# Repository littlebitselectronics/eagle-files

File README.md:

# The littleBits Eagle Files Repository

This repository contains the Eagle boards and schematics for all the littleBits modules.

littleBits circuit designs are made available pursuant to the CERN Open Hardware License Version 1.2.  This means that we publish the design files for those modules right here on github. Sharing this stuff is really important to us because littleBits products are an educational tool. Since the circuit designs for our modules are available, students can learn how they work, right down to a circuit level.  This means that people can play with littleBits modules to learn basic circuits and then come back to them later in their education for a deeper understanding of electronics or engineering.  Our founder, Ayah Bdeir, was also one of the founders of the Open Hardware Summit, a major proponent of Open Source Hardware.
To be clear, other intellectual property rights such as design elements like fonts, white soldermask with purple silkscreen, logos, as well as the modular connection system (including the connectors, the connector system and the system of modular circuits) are reserved by littleBits Electronics, Inc., and we have a number of issued patents and pending patent applications related to our proprietary magnetic connectors and our system of electrical circuits.
littleBits is a growing library of pre-assembled electronic circuits that snap together with tiny magnets. Learn more at [littlebits.cc](http://littleBits.cc).

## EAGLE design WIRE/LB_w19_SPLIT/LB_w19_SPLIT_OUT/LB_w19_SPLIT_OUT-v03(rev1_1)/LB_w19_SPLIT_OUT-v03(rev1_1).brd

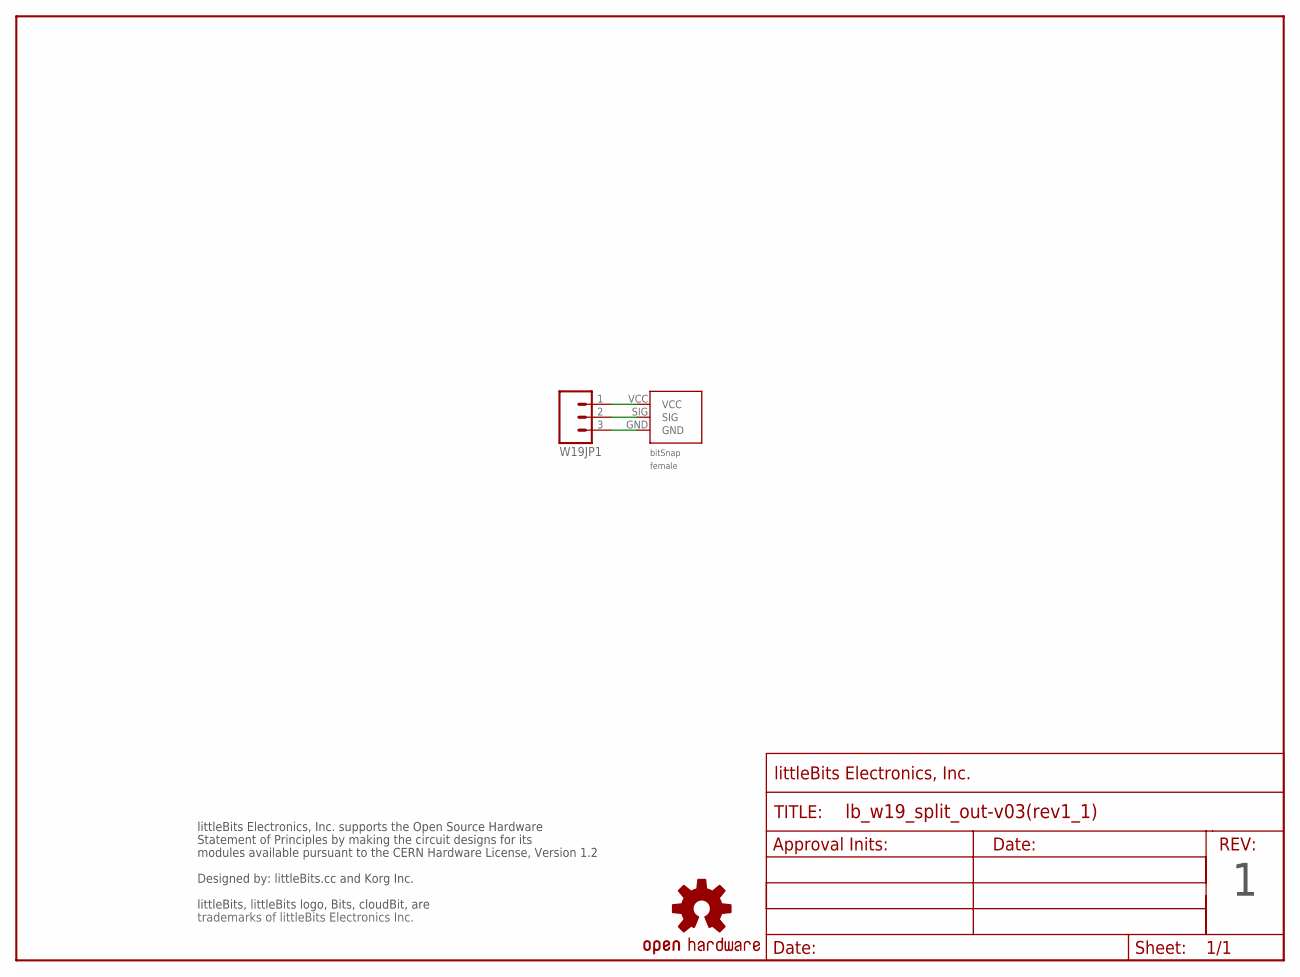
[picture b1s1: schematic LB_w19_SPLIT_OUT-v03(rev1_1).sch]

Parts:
FRAME1: FRAME-LETTER-OHWOHW; FABDWG01-OHW
U$1: OSHWCREDIT-KORG
U$3: OSHW-LOGOL; OSHW-LOGO-L
W19BSF1: BITSNAP_V03_FEMALE
W19JP1: M03SMD; 1X03-1MM-RA

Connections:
GND: W19BSF1.GND, W19JP1.3
SIG: W19BSF1.SIG, W19JP1.2
VCC: W19BSF1.VCC, W19JP1.1

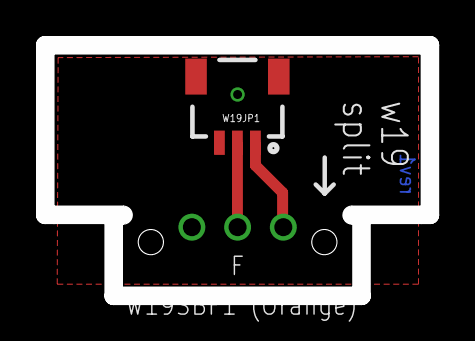
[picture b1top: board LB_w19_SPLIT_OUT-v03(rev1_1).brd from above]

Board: 2 copper layers, 21.4 x 13.9 mm, 6 parts (0 on the bottom side), 3 nets.

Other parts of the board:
U$2: OSHW_FILLX150_NOTEXT

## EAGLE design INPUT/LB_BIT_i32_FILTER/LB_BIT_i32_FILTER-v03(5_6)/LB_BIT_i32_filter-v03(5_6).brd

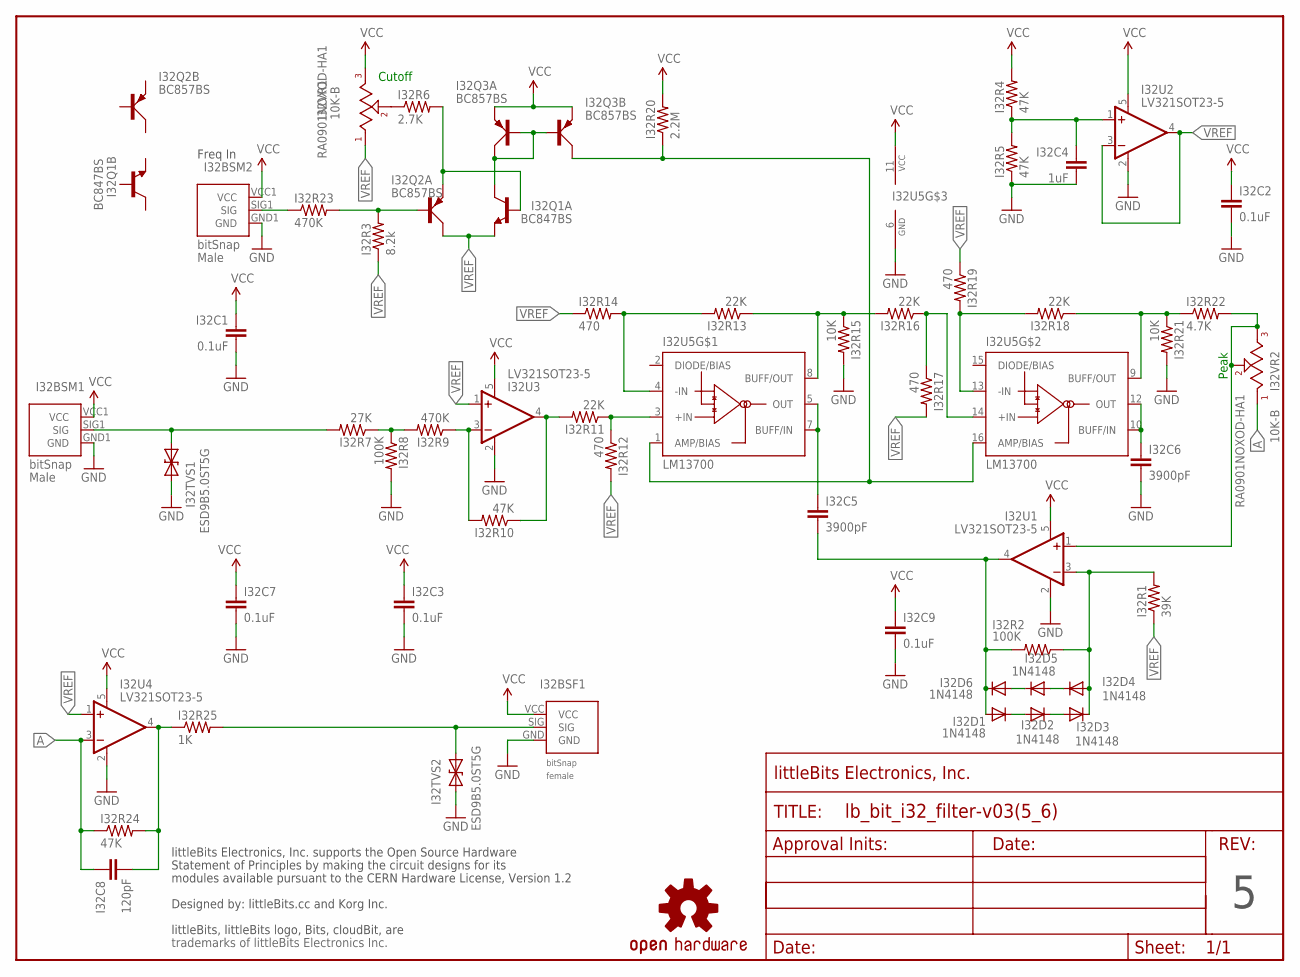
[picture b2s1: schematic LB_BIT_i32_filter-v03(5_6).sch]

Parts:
I32BSF1: BITSNAP_V03_FEMALE
I32BSM1, I32BSM2: BITSNAP_V03_MALE
I32C1, I32C2, I32C3, I32C7, I32C9: 0.1uF; CAP-0603
I32C4: 1uF; CAP-0603
I32C5, I32C6: 3900pF; CAP-0603
I32C8: 120pF; CAP-0603
I32D1, I32D2, I32D3, I32D4, I32D5, I32D6: 1N4148; SOD-323
I32Q1: BC847BS; SOT-363_PHILLIPS
I32Q2, I32Q3: BC857BS; SOT-363_PHILLIPS
I32R1: 39K; RES-0603
I32R2, I32R8: 100K; RES-0603
I32R3: 8.2k; RES-0603
I32R4, I32R5, I32R10, I32R24: 47K; RES-0603
I32R6: 2.7K; RES-0603
I32R7: 27K; RES-0603
I32R9, I32R23: 470K; RES-0603
I32R11, I32R13, I32R16, I32R18: 22K; RES-0603
I32R12, I32R14, I32R17, I32R19: 470; RES-0603
I32R15, I32R21: 10K; RES-0603
I32R20: 2.2M; RES-0603
I32R22: 4.7K; RES-0603
I32R25: 1K; RES-0603
I32TVS1, I32TVS2: ESD9B5.0ST5G; SOD-923
I32U1, I32U2, I32U3, I32U4: LV321SOT23-5; SOT23-5
I32U5: LM13700; DMP16
I32VR1, I32VR2: 10K-B; ALPS_POT
U$1: FRAME-LETTER-OHWOHW; FABDWG01-OHW
U$2: OSHWCREDIT-KORG
U$3: OSHW-LOGOL; OSHW-LOGO-L

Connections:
A: I32C8.1, I32R24.1, I32U4.3 (-IN), I32VR2.1
GND: I32BSF1.GND, I32BSM1.GND1 (GND), I32BSM2.GND1 (GND), I32C1.2, I32C2.2, I32C3.2, I32C4.2, I32C6.2, I32C7.2, I32C9.2, I32R5.1, I32R8.2, I32R15.2, I32R21.2, I32TVS1.1 (A), I32TVS2.1 (A), I32U1.2 (V-), I32U2.2 (V-), I32U3.2 (V-), I32U4.2 (V-), I32U5.6 (GND)
unnamed: I32C4.1, I32R4.1, I32R5.2, I32U2.1 (+IN)
unnamed: I32BSM1.SIG1 (SIG), I32R7.2, I32TVS1.2 (C)
unnamed: I32R6.1, I32VR1.2
unnamed: I32BSF1.SIG, I32R25.2, I32TVS2.2 (C)
unnamed: I32Q1.2 (B), I32Q2.1 (E), I32R6.2
unnamed: I32C5.2, I32D1.2 (A), I32D6.1 (C), I32R2.2, I32U1.4 (OUT)
unnamed: I32R11.1, I32R12.1, I32U5.3 (+IN)
unnamed: I32Q3.3 (C), I32R20.1, I32U5.1 (AMP/BIAS), I32U5.16 (AMP/BIAS)
unnamed: I32R7.1, I32R8.1, I32R9.2
unnamed: I32R9.1, I32R10.2, I32U3.3 (-IN)
unnamed: I32R10.1, I32R11.2, I32U3.4 (OUT)
unnamed: I32R13.2, I32R14.2, I32U5.4 (-IN)
unnamed: I32R18.2, I32R19.2, I32U5.13 (-IN)
unnamed: I32R13.1, I32R15.1, I32R16.2, I32U5.8 (BUFF/OUT)
unnamed: I32C5.1, I32U5.5 (OUT), I32U5.7 (BUFF/IN)
unnamed: I32R22.2, I32U1.1 (+IN), I32VR2.2, I32VR2.3
unnamed: I32R16.1, I32R17.1, I32U5.14 (+IN)
unnamed: I32R18.1, I32R21.1, I32R22.1, I32U5.9 (BUFF/OUT)
unnamed: I32C6.1, I32U5.10 (BUFF/IN), I32U5.12 (OUT)
unnamed: I32C8.2, I32R24.2, I32R25.1, I32U4.4 (OUT)
unnamed: I32D3.1 (C), I32D4.2 (A), I32R1.2, I32R2.1, I32U1.3 (-IN)
unnamed: I32Q2.2 (B), I32R3.2, I32R23.2
unnamed: I32BSM2.SIG1 (SIG), I32R23.1
unnamed: I32D4.1 (C), I32D5.2 (A)
unnamed: I32D5.1 (C), I32D6.2 (A)
unnamed: I32D1.1 (C), I32D2.2 (A)
unnamed: I32D2.1 (C), I32D3.2 (A)
unnamed: I32Q1.6 (C), I32Q3.2 (B), I32Q3.5 (B), I32Q3.6 (C)
VCC: I32BSF1.VCC, I32BSM1.VCC1 (VCC), I32BSM2.VCC1 (VCC), I32C1.1, I32C2.1, I32C3.1, I32C7.1, I32C9.1, I32Q3.1 (E), I32Q3.4 (E), I32R4.2, I32R20.2, I32U1.5 (V+), I32U2.5 (V+), I32U3.5 (V+), I32U4.5 (V+), I32U5.11 (VCC), I32VR1.3
VREF: I32Q1.1 (E), I32Q2.6 (C), I32R1.1, I32R3.1, I32R12.2, I32R14.1, I32R17.2, I32R19.1, I32U2.3 (-IN), I32U2.4 (OUT), I32U3.1 (+IN), I32U4.1 (+IN), I32VR1.1

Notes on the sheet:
Peak
Cutoff
Freq In
RA0901NOXOD-HA1

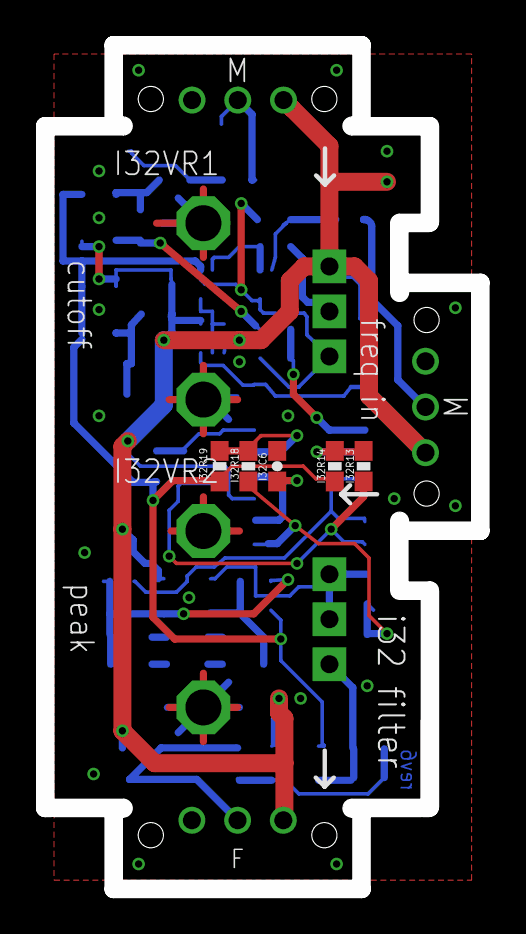
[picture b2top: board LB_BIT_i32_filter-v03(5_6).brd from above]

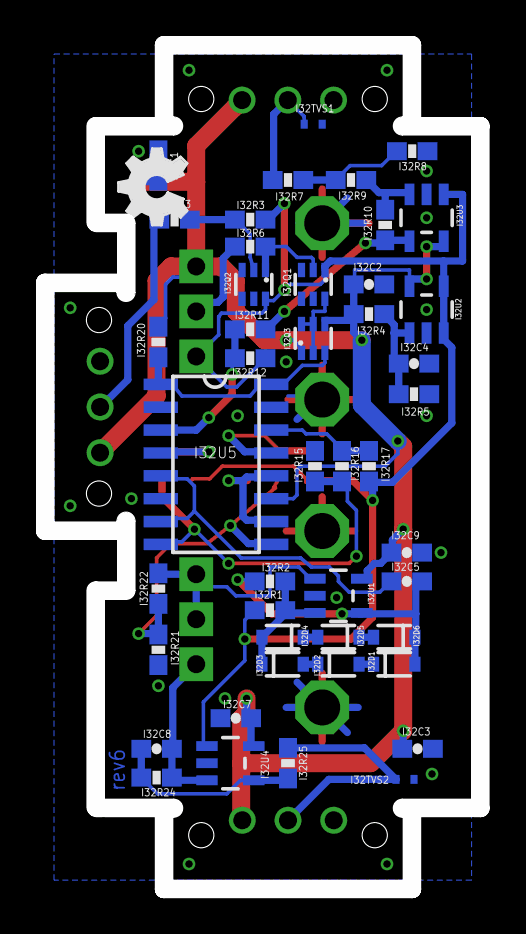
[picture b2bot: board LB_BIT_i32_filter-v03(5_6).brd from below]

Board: 2 copper layers, 24.2 x 46.9 mm, 59 parts (45 on the bottom side), 32 nets.

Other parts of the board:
U$8: OSHW_FILLX150_NOTEXT

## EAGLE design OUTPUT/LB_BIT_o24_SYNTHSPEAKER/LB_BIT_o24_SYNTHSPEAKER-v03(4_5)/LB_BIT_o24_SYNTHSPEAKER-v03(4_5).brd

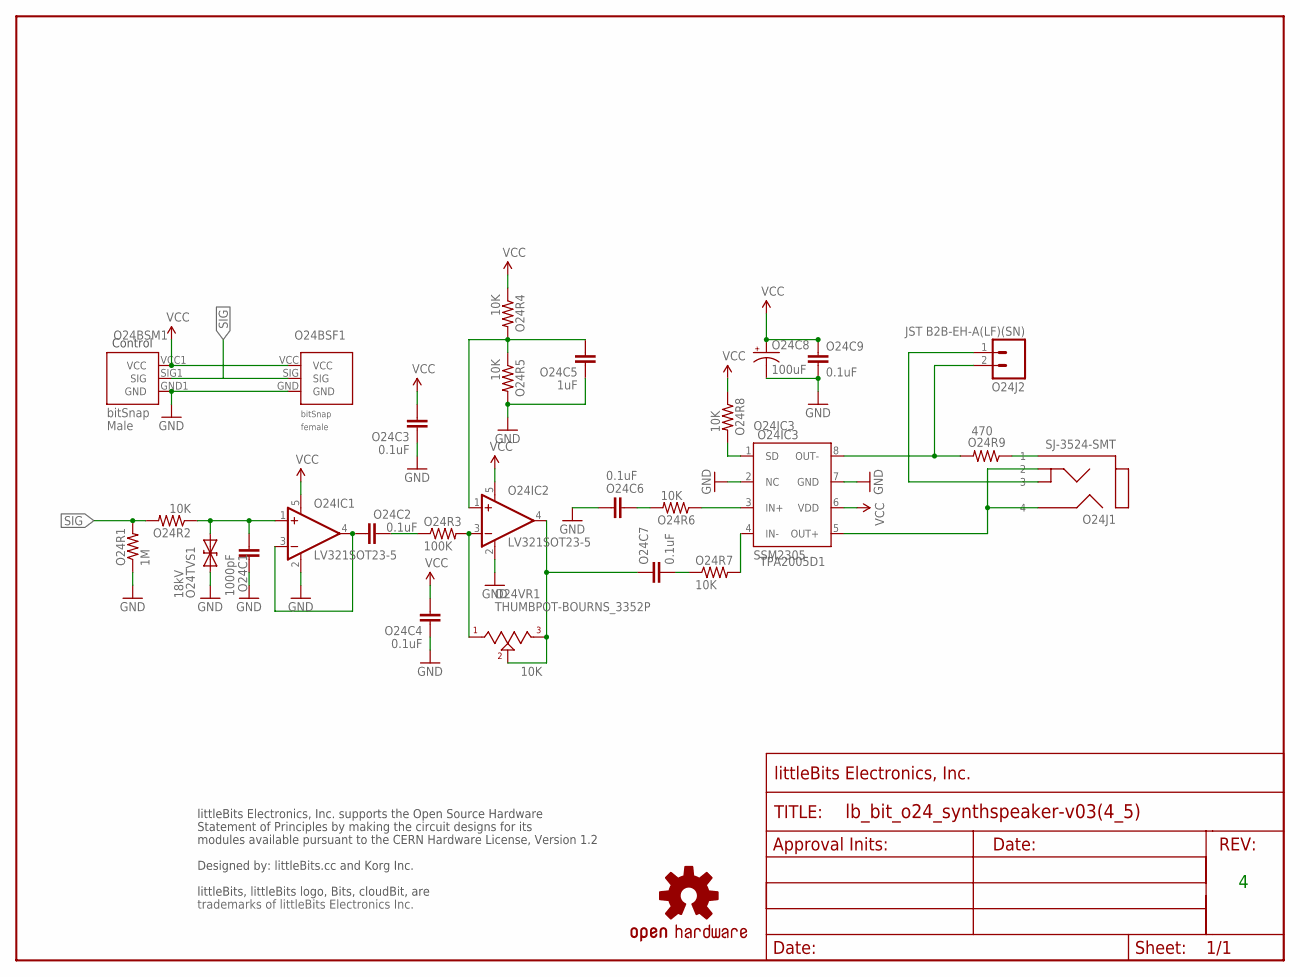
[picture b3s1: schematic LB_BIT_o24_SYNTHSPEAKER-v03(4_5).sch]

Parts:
$1_28_$: OSHW-LOGOL; OSHW-LOGO-L
FRAME1: FRAME-LETTER-OHWOHW; FABDWG01-OHW
O24BSF1: BITSNAP_V03_FEMALE
O24BSM1: BITSNAP_V03_MALE
O24C1: 1000pF; CAP-0603
O24C2, O24C3, O24C4, O24C6, O24C7, O24C9: 0.1uF; CAP-0603
O24C5: 1uF; CAP-0603
O24C8: 100uF; EIA3216
O24IC1, O24IC2: LV321SOT23-5; SOT23-5
O24IC3: SSM2305; MSOP08
O24J1: SJ-3524-SMT; PHONO_JACK_SW
O24J2: JST B2B-EH-A(LF)(SN); H02-JST-B2B-EH-A
O24R1: 1M; RES-0603
O24R2, O24R4, O24R5, O24R6, O24R7, O24R8: 10K; RES-0603
O24R3: 100K; RES-0603
O24R9: 470; RES-0603
O24TVS1: 18kV; SOD-923
O24VR1: THUMBPOT-BOURNS_3352P; THUMBPOT-BOURNS_3352
U$1: OSHWCREDIT-KORG

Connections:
BIT_SIG: O24C2.2, O24IC1.3 (-IN), O24IC1.4 (OUT)
GND: O24BSF1.GND, O24BSM1.GND1 (GND), O24C1.1, O24C3.1, O24C4.1, O24C5.1, O24C6.2, O24C8.-, O24C9.2, O24IC1.2 (V-), O24IC2.2 (V-), O24IC3.2 (NC), O24IC3.7 (GND), O24R1.1, O24R5.2, O24TVS1.1 (A)
unnamed: O24J1.3, O24J2.1
unnamed: O24IC3.1 (SD), O24R8.2
unnamed: O24IC3.5 (OUT+), O24J1.2, O24J1.4
unnamed: O24C6.1, O24R6.2
unnamed: O24J1.1, O24R9.1
unnamed: O24IC3.3 (IN+), O24R6.1
unnamed: O24IC2.3 (-IN), O24R3.2, O24VR1.3 (1)
unnamed: O24C7.1, O24IC2.4 (OUT), O24VR1.1 (3), O24VR1.2
unnamed: O24C5.2, O24IC2.1 (+IN), O24R4.2, O24R5.1
unnamed: O24C7.2, O24R7.1
unnamed: O24C2.1, O24R3.1
unnamed: O24IC3.4 (IN-), O24R7.2
unnamed: O24C1.2, O24IC1.1 (+IN), O24R2.1, O24TVS1.2 (C)
SIG: O24BSF1.SIG, O24BSM1.SIG1 (SIG), O24R1.2, O24R2.2
SPKR_SW: O24IC3.8 (OUT-), O24J2.2, O24R9.2
VCC: O24BSF1.VCC, O24BSM1.VCC1 (VCC), O24C3.2, O24C4.2, O24C8.+, O24C9.1, O24IC1.5 (V+), O24IC2.5 (V+), O24IC3.6 (VDD), O24R4.1, O24R8.1

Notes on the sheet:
TPA2005D1
Control
10K
O24IC3

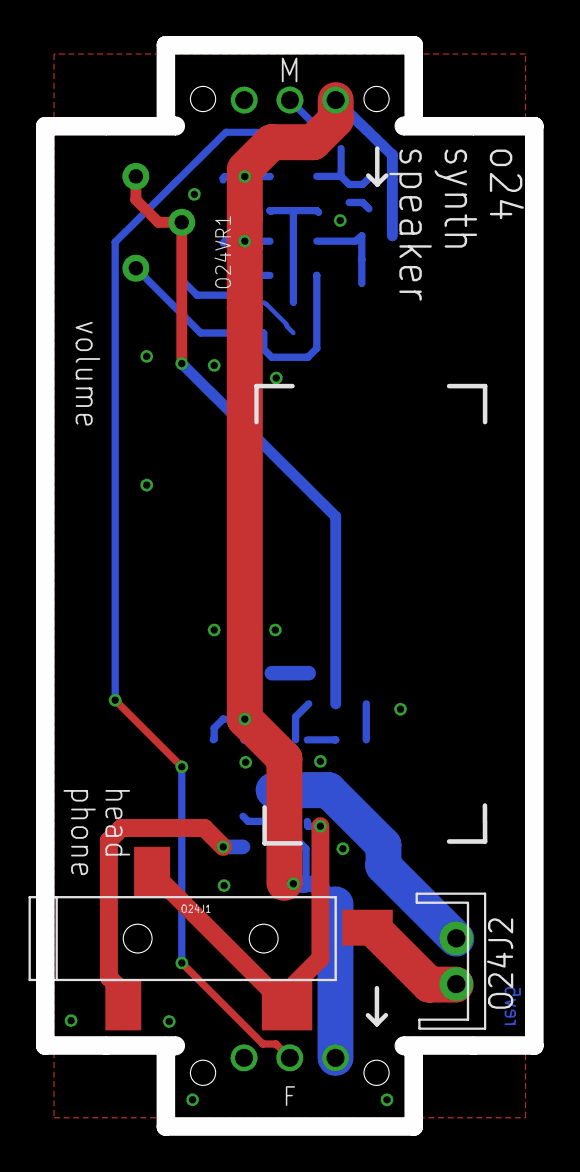
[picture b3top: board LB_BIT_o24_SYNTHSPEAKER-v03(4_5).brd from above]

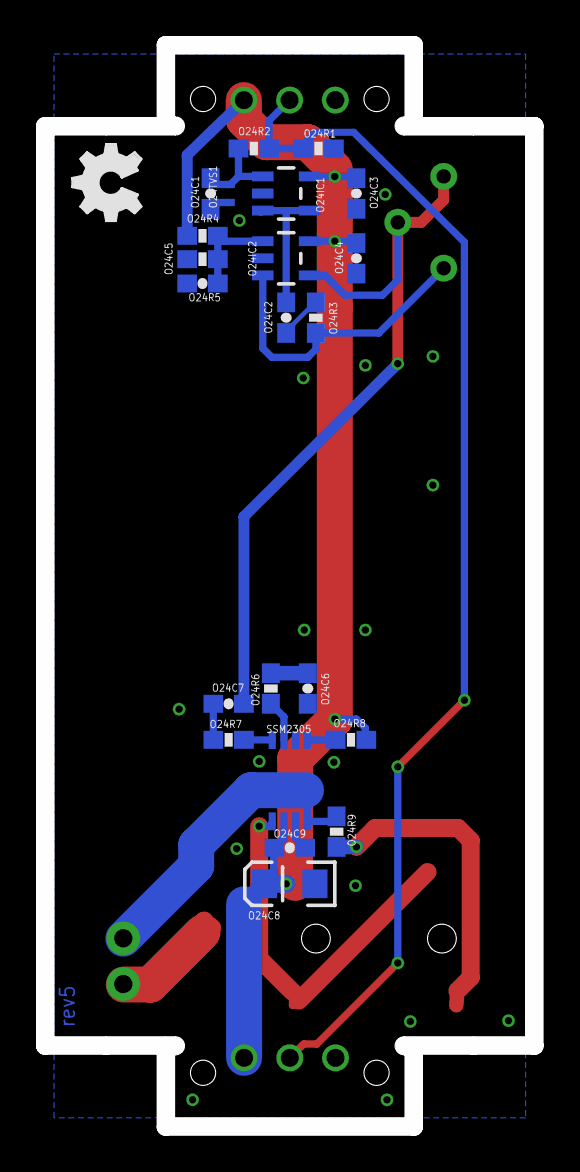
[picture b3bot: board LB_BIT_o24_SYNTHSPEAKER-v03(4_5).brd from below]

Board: 2 copper layers, 27.2 x 60.1 mm, 31 parts (22 on the bottom side), 18 nets.

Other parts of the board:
U$8: OSHW_FILLX150_NOTEXT

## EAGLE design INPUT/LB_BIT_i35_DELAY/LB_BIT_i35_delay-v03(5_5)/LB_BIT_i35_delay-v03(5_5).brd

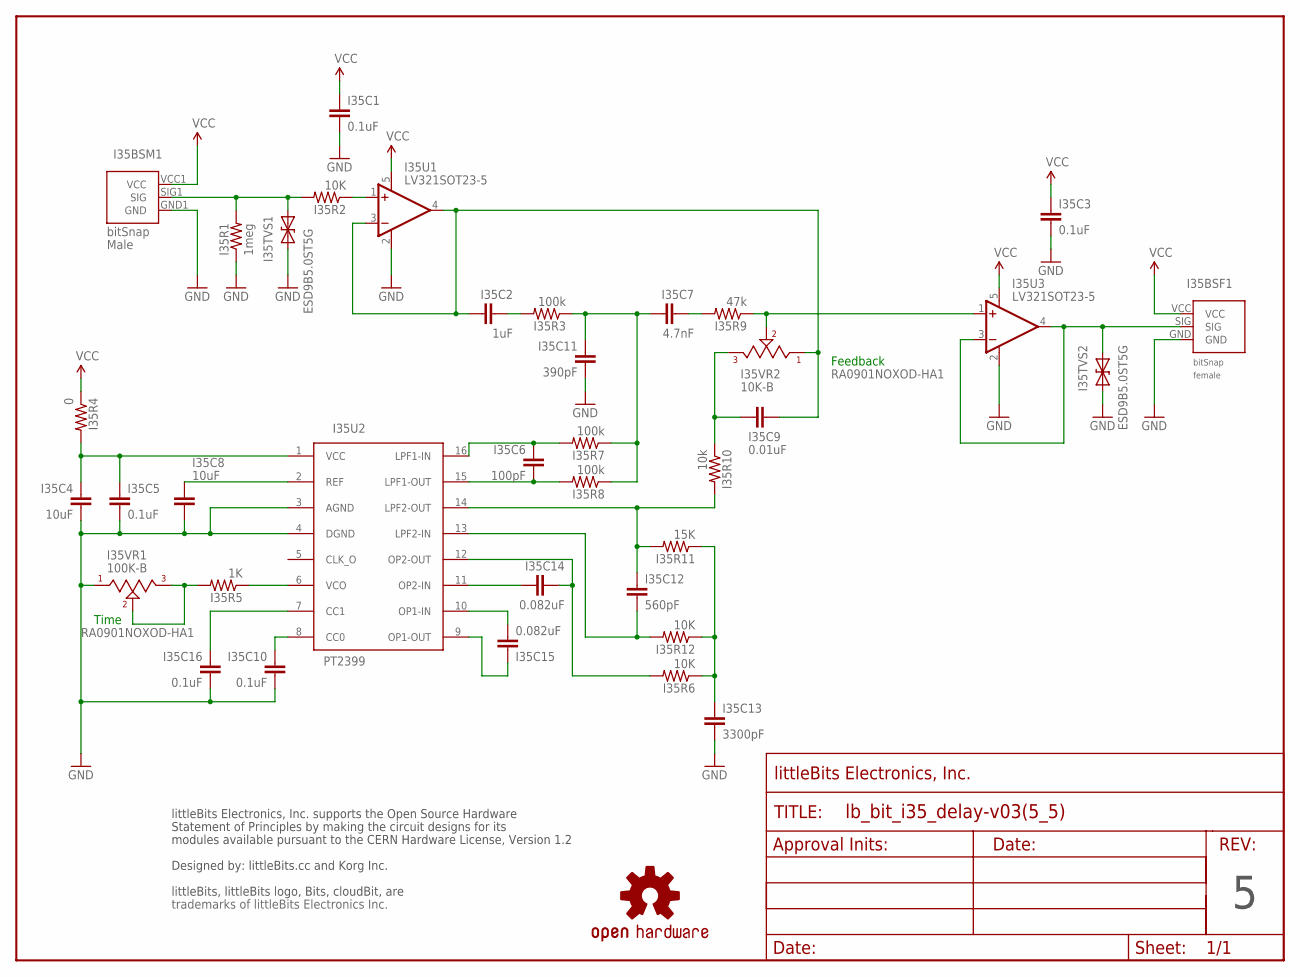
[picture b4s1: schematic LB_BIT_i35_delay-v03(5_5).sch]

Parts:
I35BSF1: BITSNAP_V03_FEMALE
I35BSM1: BITSNAP_V03_MALE
I35C1, I35C3, I35C5, I35C10, I35C16: 0.1uF; CAP-0603
I35C2: 1uF; CAP-0603
I35C4, I35C8: 10uF; CAP-0603
I35C6: 100pF; CAP-0603
I35C7: 4.7nF; CAP-0603
I35C9: 0.01uF; CAP-0603
I35C11: 390pF; CAP-0603
I35C12: 560pF; CAP-0603
I35C13: 3300pF; CAP-0603
I35C14, I35C15: 0.082uF; CAP-0603
I35R1: 1meg; RES-0603
I35R2, I35R6, I35R12: 10K; RES-0603
I35R3, I35R7, I35R8: 100k; RES-0603
I35R4: 0; RES-0603
I35R5: 1K; RES-0603
I35R9: 47k; RES-0603
I35R10: 10k; RES-0603
I35R11: 15K; RES-0603
I35TVS1, I35TVS2: ESD9B5.0ST5G; SOD-923
I35U1, I35U3: LV321SOT23-5; SOT23-5
I35U2: PT2399; SO16
I35VR1: 100K-B; ALPS_POT
I35VR2: 10K-B; ALPS_POT
U$1: FRAME-LETTER-OHWOHW; FABDWG01-OHW
U$2: OSHWCREDIT-KORG
U$3: OSHW-LOGOL; OSHW-LOGO-L

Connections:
GND: I35BSF1.GND, I35BSM1.GND1 (GND), I35C1.2, I35C3.2, I35C4.2, I35C5.2, I35C8.2, I35C10.2, I35C11.2, I35C13.2, I35C16.2, I35R1.1, I35TVS1.1 (A), I35TVS2.1 (A), I35U1.2 (V-), I35U2.3 (AGND), I35U2.4 (DGND), I35U3.2 (V-), I35VR1.1
unnamed: I35C2.2, I35R3.2
unnamed: I35R2.1, I35U1.1 (+IN)
unnamed: I35C7.1, I35C11.1, I35R3.1, I35R7.1, I35R8.1
unnamed: I35C6.2, I35R8.2, I35U2.15 (LPF1-OUT)
unnamed: I35C6.1, I35R7.2, I35U2.16 (LPF1-IN)
unnamed: I35R9.1, I35U3.1 (+IN), I35VR2.2
unnamed: I35C7.2, I35R9.2
unnamed: I35C9.1, I35R10.1, I35VR2.3
unnamed: I35C2.1, I35C9.2, I35U1.3 (-IN), I35U1.4 (OUT), I35VR2.1
unnamed: I35C12.1, I35R10.2, I35R11.2, I35U2.14 (LPF2-OUT)
unnamed: I35C12.2, I35R12.2, I35U2.13 (LPF2-IN)
unnamed: I35C13.1, I35R6.1, I35R11.1, I35R12.1
unnamed: I35C14.2, I35R6.2, I35U2.12 (OP2-OUT)
unnamed: I35C14.1, I35U2.11 (OP2-IN)
unnamed: I35C15.2, I35U2.10 (OP1-IN)
unnamed: I35C15.1, I35U2.9 (OP1-OUT)
unnamed: I35C10.1, I35U2.8 (CC0)
unnamed: I35C16.1, I35U2.7 (CC1)
unnamed: I35R5.2, I35VR1.2, I35VR1.3
unnamed: I35R5.1, I35U2.6 (VCO)
unnamed: I35C8.1, I35U2.2 (REF)
unnamed: I35C4.1, I35C5.1, I35R4.2, I35U2.1 (VCC)
SIG_IN: I35BSM1.SIG1 (SIG), I35R1.2, I35R2.2, I35TVS1.2 (C)
SIG_OUT: I35BSF1.SIG, I35TVS2.2 (C), I35U3.3 (-IN), I35U3.4 (OUT)
VCC: I35BSF1.VCC, I35BSM1.VCC1 (VCC), I35C1.1, I35C3.1, I35R4.1, I35U1.5 (V+), I35U3.5 (V+)

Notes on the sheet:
Feedback
Time
RA0901NOXOD-HA1

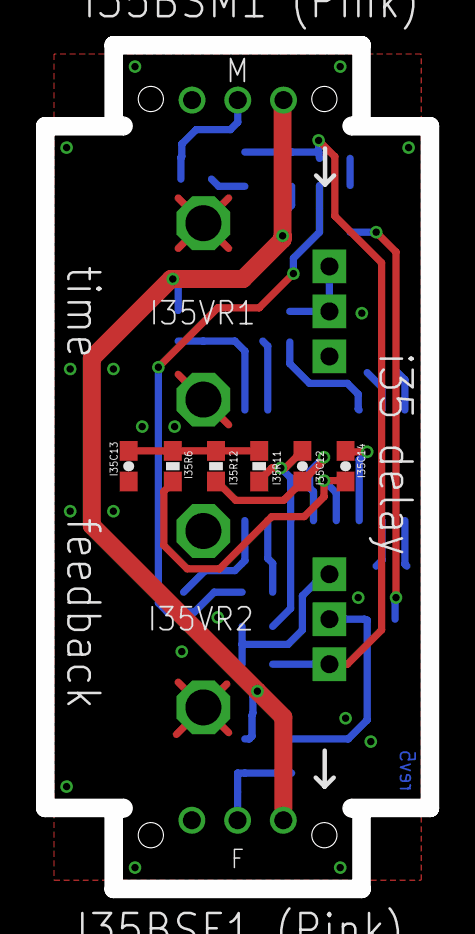
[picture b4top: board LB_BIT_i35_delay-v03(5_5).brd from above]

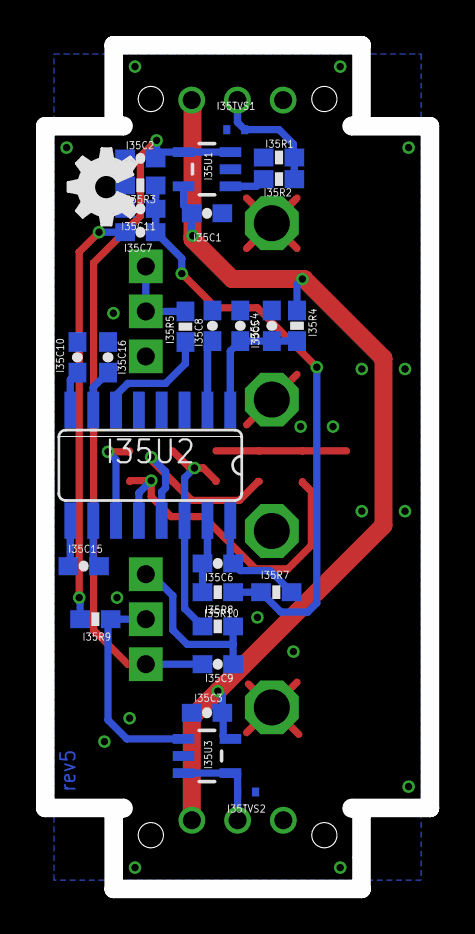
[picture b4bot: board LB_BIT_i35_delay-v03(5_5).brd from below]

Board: 2 copper layers, 21.4 x 46.9 mm, 41 parts (27 on the bottom side), 26 nets.

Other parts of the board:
E$1: FABDWG01-OHW
E$2: OSHWCREDIT-KORG
U$8: OSHW_FILLX150_NOTEXT

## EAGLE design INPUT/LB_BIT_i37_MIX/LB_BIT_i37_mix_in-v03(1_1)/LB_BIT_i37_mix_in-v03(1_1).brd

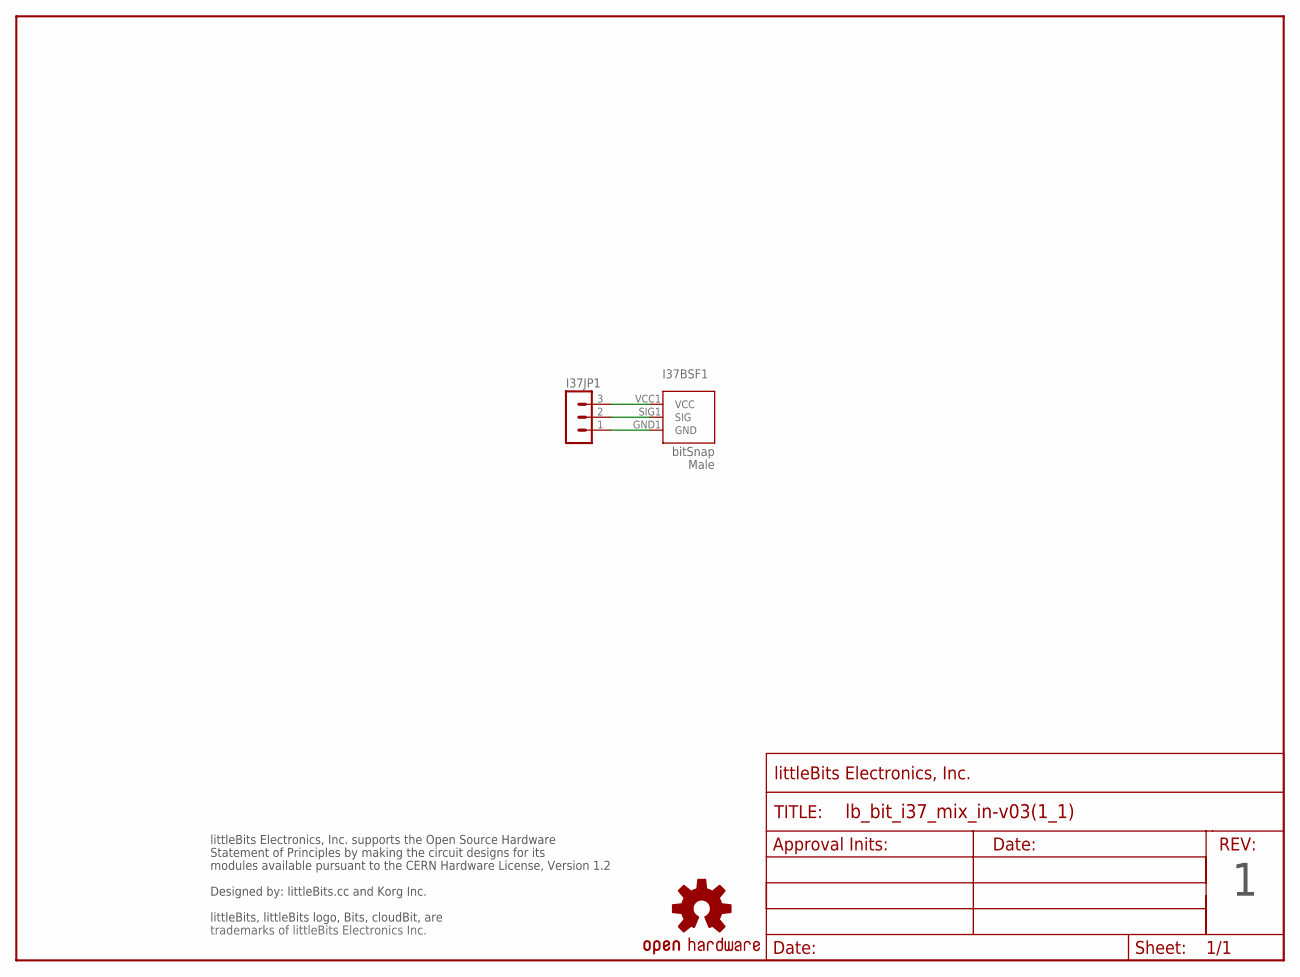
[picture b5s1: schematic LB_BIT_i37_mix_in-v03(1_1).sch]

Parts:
I37BSF1: BITSNAP_V03_MALE
I37JP1: MA03-1SMD; 1X03-1MM-RA
U$1: FRAME-LETTER-OHWOHW; FABDWG01-OHW
U$3: OSHW-LOGOL; OSHW-LOGO-L
U$4: OSHWCREDIT-KORG

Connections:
GND: I37BSF1.GND1 (GND), I37JP1.1
SIG: I37BSF1.SIG1 (SIG), I37JP1.2
VCC: I37BSF1.VCC1 (VCC), I37JP1.3

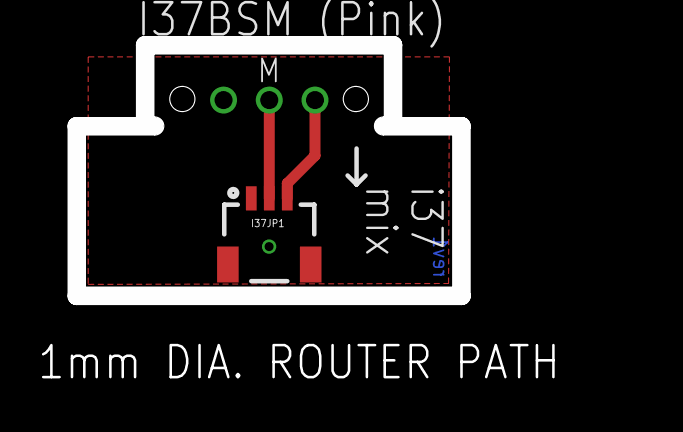
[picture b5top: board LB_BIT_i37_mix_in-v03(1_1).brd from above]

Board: 2 copper layers, 32.9 x 19.0 mm, 6 parts (0 on the bottom side), 3 nets.

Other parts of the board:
U$2: OSHW_FILLX150_NOTEXT

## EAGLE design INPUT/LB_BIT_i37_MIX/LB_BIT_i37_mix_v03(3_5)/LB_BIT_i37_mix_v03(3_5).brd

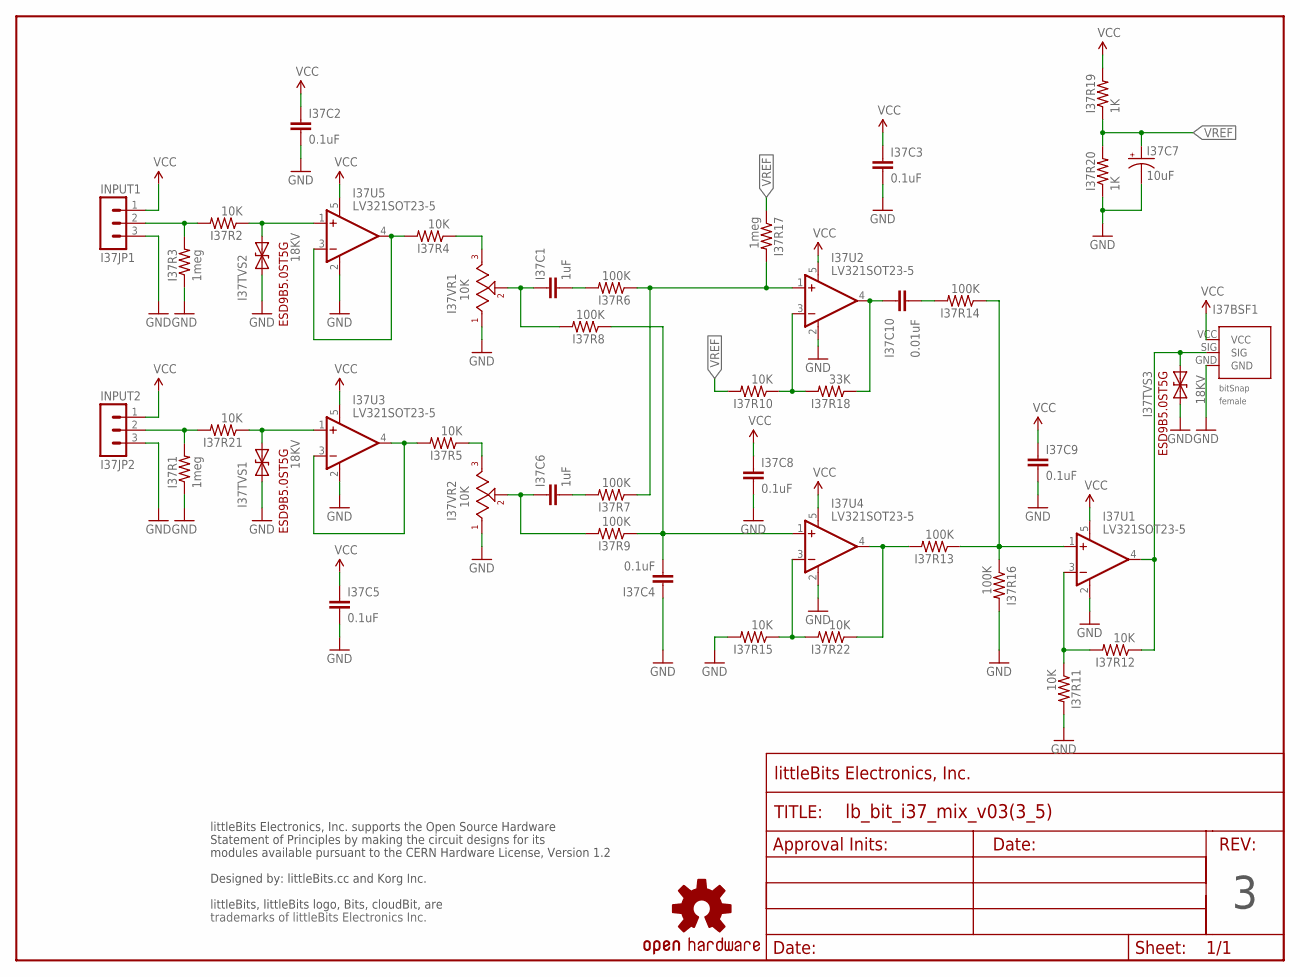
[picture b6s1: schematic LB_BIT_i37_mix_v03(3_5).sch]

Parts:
I37BSF1: BITSNAP_V03_FEMALE
I37C1, I37C6: 1uF; CAP-0603
I37C2, I37C3, I37C4, I37C5, I37C8, I37C9: 0.1uF; CAP-0603
I37C7: 10uF; EIA3216
I37C10: 0.01uF; CAP-0603
I37JP1: INPUT1; 1X03-1MM-RA
I37JP2: INPUT2; 1X03-1MM-RA
I37R1, I37R3, I37R17: 1meg; RES-0603
I37R2, I37R4, I37R5, I37R10, I37R11, I37R12, I37R15, I37R21, I37R22: 10K; RES-0603
I37R6, I37R7, I37R8, I37R9, I37R13, I37R14, I37R16: 100K; RES-0603
I37R18: 33K; RES-0603
I37R19, I37R20: 1K; RES-0603
I37TVS1, I37TVS2, I37TVS3: 18KV; SOD-923
I37U1, I37U2, I37U3, I37U4, I37U5: LV321SOT23-5; SOT23-5
I37VR1, I37VR2: 10K; ALPS_POT
U$1: OSHWCREDIT-KORG
U$2: FRAME-LETTER-OHWOHW; FABDWG01-OHW
U$19: OSHW-LOGOL; OSHW-LOGO-L

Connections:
GND: I37BSF1.GND, I37C2.2, I37C3.2, I37C4.1, I37C5.2, I37C7.-, I37C8.2, I37C9.2, I37JP1.3, I37JP2.3, I37R1.1, I37R3.1, I37R11.2, I37R15.2, I37R16.2, I37R20.1, I37TVS1.1 (A), I37TVS2.1 (A), I37TVS3.1 (A), I37U1.2 (V-), I37U2.2 (V-), I37U3.2 (V-), I37U4.2 (V-), I37U5.2 (V-), I37VR1.1, I37VR2.1
unnamed: I37JP2.2, I37R1.2, I37R21.2
unnamed: I37R5.2, I37U3.3 (-IN), I37U3.4 (OUT)
unnamed: I37JP1.2, I37R2.2, I37R3.2
unnamed: I37R21.1, I37TVS1.2 (C), I37U3.1 (+IN)
unnamed: I37R4.1, I37VR1.3
unnamed: I37R2.1, I37TVS2.2 (C), I37U5.1 (+IN)
unnamed: I37R4.2, I37U5.3 (-IN), I37U5.4 (OUT)
unnamed: I37C1.1, I37R8.2, I37VR1.2
unnamed: I37R5.1, I37VR2.3
unnamed: I37C6.1, I37R9.2, I37VR2.2
unnamed: I37C6.2, I37R7.2
unnamed: I37C1.2, I37R6.2
unnamed: I37C4.2, I37R8.1, I37R9.1, I37U4.1 (+IN)
unnamed: I37R6.1, I37R7.1, I37R17.2, I37U2.1 (+IN)
unnamed: I37R10.1, I37R18.2, I37U2.3 (-IN)
unnamed: I37C10.1, I37R18.1, I37U2.4 (OUT)
unnamed: I37R15.1, I37R22.2, I37U4.3 (-IN)
unnamed: I37R13.2, I37R22.1, I37U4.4 (OUT)
unnamed: I37R13.1, I37R14.1, I37R16.1, I37U1.1 (+IN)
unnamed: I37R11.1, I37R12.2, I37U1.3 (-IN)
unnamed: I37BSF1.SIG, I37R12.1, I37TVS3.2 (C), I37U1.4 (OUT)
unnamed: I37C10.2, I37R14.2
VCC: I37BSF1.VCC, I37C2.1, I37C3.1, I37C5.1, I37C8.1, I37C9.1, I37JP1.1, I37JP2.1, I37R19.2, I37U1.5 (V+), I37U2.5 (V+), I37U3.5 (V+), I37U4.5 (V+), I37U5.5 (V+)
VREF: I37C7.+, I37R10.2, I37R17.1, I37R19.1, I37R20.2

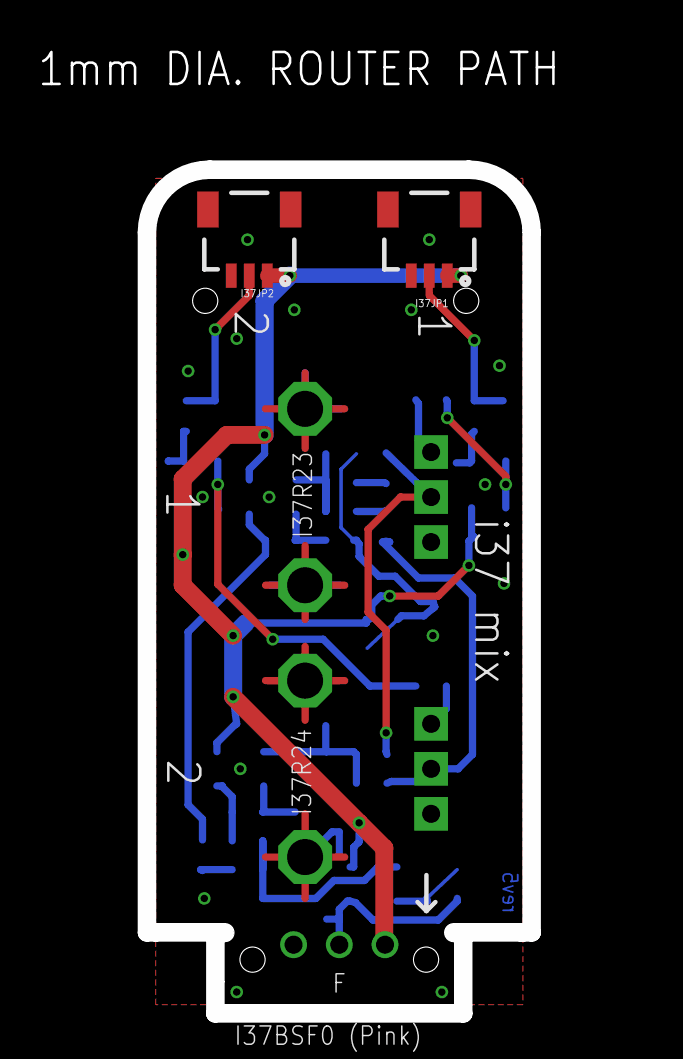
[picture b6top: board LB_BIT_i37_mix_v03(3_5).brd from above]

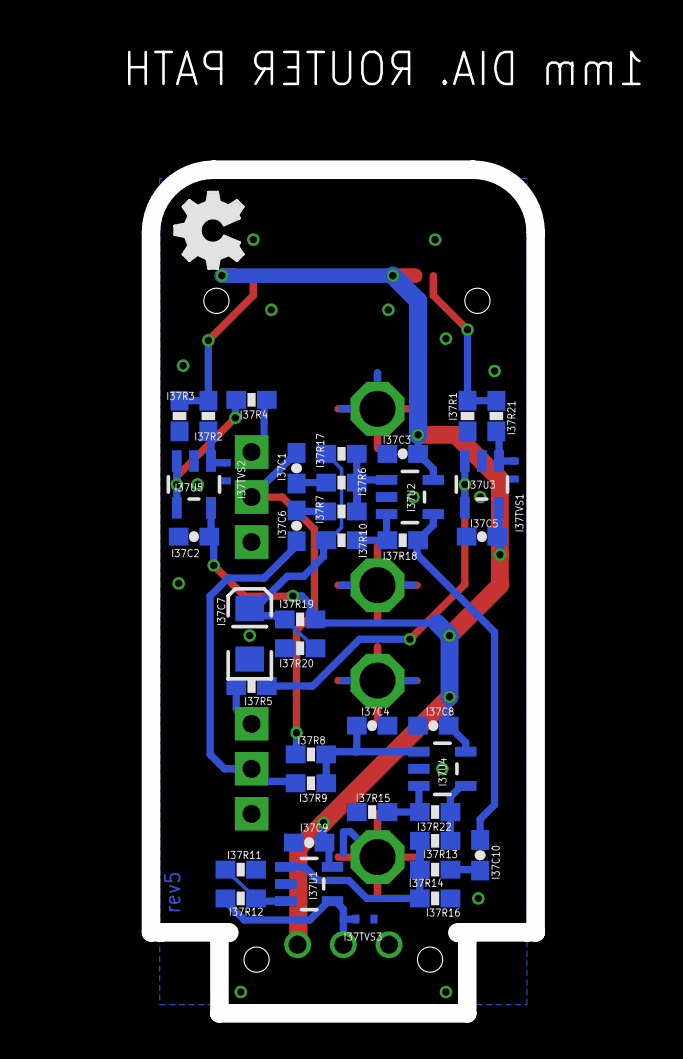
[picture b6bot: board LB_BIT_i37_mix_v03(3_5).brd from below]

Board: 2 copper layers, 32.9 x 53.8 mm, 50 parts (40 on the bottom side), 25 nets.

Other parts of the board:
U$5: LB_PWR_LEGS
U$8: OSHW_FILLX150_NOTEXT

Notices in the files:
parts and their libraries:
LITTLEBITS: modules available pursuant to the CERN Hardware License, Version 1.2
SparkFun_NEW: Licensing: CC v3.0 Share-Alike You are welcome to use this library for commercial purposes.
